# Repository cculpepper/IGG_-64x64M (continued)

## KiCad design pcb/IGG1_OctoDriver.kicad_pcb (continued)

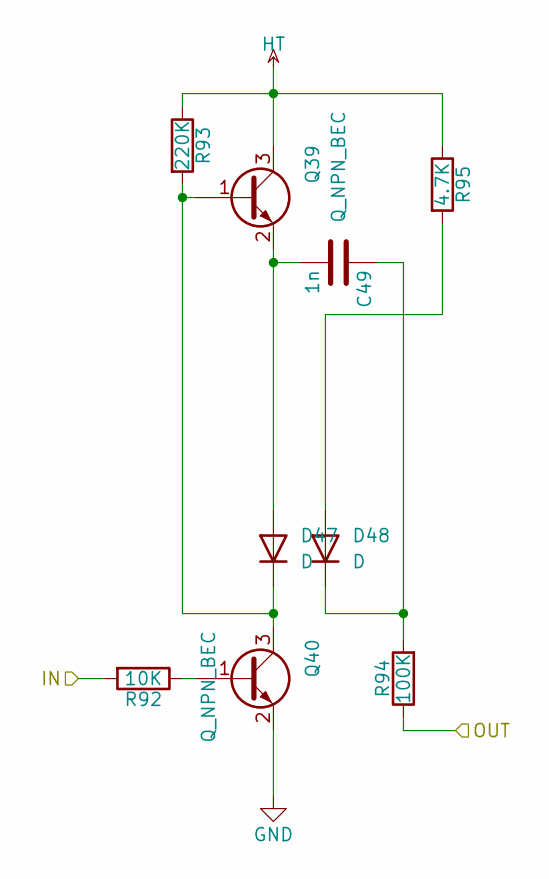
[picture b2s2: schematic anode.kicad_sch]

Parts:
C49: 1n; C_1206_3216Metric; LCSC C9196
D47, D48: D; D_SOD-323; LCSC C896450
Q39, Q40: Q_NPN_BEC; SOT-23; LCSC C20069141
R92: 10K; R_0603_1608Metric; LCSC C25804
R93: 220K; R_1206_3216Metric; LCSC C17956
R94: 100K; R_1206_3216Metric; LCSC C17900
R95: 4.7K; R_1206_3216Metric; LCSC C17936

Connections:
/AI18: R92.2; also elsewhere on the board
/AO18: R94.1; also elsewhere on the board
GND: Q40.2 (E); also elsewhere on the board
HT: Q39.3 (C), R93.1, R95.1; also elsewhere on the board
unnamed: C49.2, D47.2 (A), Q39.2 (E)
unnamed: D47.1 (K), Q39.1 (B), Q40.3 (C), R93.2
unnamed: D48.2 (A), R95.2
unnamed: C49.1, D48.1 (K), R94.2
unnamed: Q40.1 (B), R92.1

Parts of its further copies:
C30, C31, C32, C33, C34, C35, C36, C37, C38, C39, C40, C41, C42, C43, C44, C45, C46, C47, C48, C50, C51, C52, C53, C54, C55, C56, C57, C58, C59, C60, C61, C62, C63, C64, C65, C66, C67, C68, C69, C70, C71, C72, C73, C74, C75, C76, C77, C78, C79, C80, C81, C82, C83, C84, C85, C86, C87, C88, C89, C90, C91, C92, C93: 1n; C_1206_3216Metric; LCSC C9196
D9, D10, D11, D12, D13, D14, D15, D16, D17, D18, D19, D20, D21, D22, D23, D24, D25, D26, D27, D28, D29, D30, D31, D32, D33, D34, D35, D36, D37, D38, D39, D40, D41, D42, D43, D44, D45, D46, D49, D50, D51, D52, D53, D54, D55, D56, D57, D58, D59, D60, D61, D62, D63, D64, D65, D66, D67, D68, D69, D70, D71, D72, D73, D74, D75, D76, D77, D78, D79, D80, D81, D82, D83, D84, D85, D86, D87, D88, D89, D90, D91, D92, D93, D94, D95, D96, D97, D98, D99, D100, D101, D102, D103, D104, D105, D106, D107, D108, D109, D110, D111, D112, D113, D114, D115, D116, D117, D118, D119, D120, D121, D122, D123, D124, D125, D126, D127, D128, D129, D130, D131, D132, D133, D134, D135, D136: D; D_SOD-323; LCSC C896450
Q1, Q2, Q3, Q4, Q5, Q6, Q7, Q8, Q9, Q10, Q11, Q12, Q13, Q14, Q15, Q16, Q17, Q18, Q19, Q20, Q21, Q22, Q23, Q24, Q25, Q26, Q27, Q28, Q29, Q30, Q31, Q32, Q33, Q34, Q35, Q36, Q37, Q38, Q41, Q42, Q43, Q44, Q45, Q46, Q47, Q48, Q49, Q50, Q51, Q52, Q53, Q54, Q55, Q56, Q57, Q58, Q59, Q60, Q61, Q62, Q63, Q64, Q65, Q66, Q67, Q68, Q69, Q70, Q71, Q72, Q73, Q74, Q75, Q76, Q77, Q78, Q79, Q80, Q81, Q82, Q83, Q84, Q85, Q86, Q87, Q88, Q89, Q90, Q91, Q92, Q93, Q94, Q95, Q96, Q97, Q98, Q99, Q100, Q101, Q102, Q103, Q104, Q105, Q106, Q107, Q108, Q109, Q110, Q111, Q112, Q113, Q114, Q115, Q116, Q117, Q118, Q119, Q120, Q121, Q122, Q123, Q124, Q125, Q126, Q127, Q128: Q_NPN_BEC; SOT-23; LCSC C20069141
R16, R20, R24, R28, R32, R36, R40, R44, R48, R52, R56, R60, R64, R68, R72, R76, R80, R84, R88, R96, R100, R104, R108, R112, R116, R120, R124, R128, R132, R136, R140, R144, R148, R152, R156, R160, R164, R168, R172, R176, R180, R184, R188, R192, R196, R200, R204, R208, R212, R216, R220, R224, R228, R232, R236, R240, R244, R248, R252, R256, R260, R264, R268: 10K; R_0603_1608Metric; LCSC C25804
R17, R21, R25, R29, R33, R37, R41, R45, R49, R53, R57, R61, R65, R69, R73, R77, R81, R85, R89, R97, R101, R105, R109, R113, R117, R121, R125, R129, R133, R137, R141, R145, R149, R153, R157, R161, R165, R169, R173, R177, R181, R185, R189, R193, R197, R201, R205, R209, R213, R217, R221, R225, R229, R233, R237, R241, R245, R249, R253, R257, R261, R265, R269: 220K; R_1206_3216Metric; LCSC C17956
R18, R22, R26, R30, R34, R38, R42, R46, R50, R54, R58, R62, R66, R70, R74, R78, R82, R86, R90, R98, R102, R106, R110, R114, R118, R122, R126, R130, R134, R138, R142, R146, R150, R154, R158, R162, R166, R170, R174, R178, R182, R186, R190, R194, R198, R202, R206, R210, R214, R218, R222, R226, R230, R234, R238, R242, R246, R250, R254, R258, R262, R266, R270: 100K; R_1206_3216Metric; LCSC C17900
R19, R23, R27, R31, R35, R39, R43, R47, R51, R55, R59, R63, R67, R71, R75, R79, R83, R87, R91, R99, R103, R107, R111, R115, R119, R123, R127, R131, R135, R139, R143, R147, R151, R155, R159, R163, R167, R171, R175, R179, R183, R187, R191, R195, R199, R203, R207, R211, R215, R219, R223, R227, R231, R235, R239, R243, R247, R251, R255, R259, R263, R267, R271: 4.7K; R_1206_3216Metric; LCSC C17936

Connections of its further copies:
/AI1: R16.2; also elsewhere on the board
/AI2: R20.2; also elsewhere on the board
/AI3: R24.2; also elsewhere on the board
/AI4: R28.2; also elsewhere on the board
/AI5: R32.2; also elsewhere on the board
/AI6: R44.2; also elsewhere on the board
/AI7: R36.2; also elsewhere on the board
/AI8: R40.2; also elsewhere on the board
/AI9: R48.2; also elsewhere on the board
/AI10: R60.2; also elsewhere on the board
/AI11: R52.2; also elsewhere on the board
/AI12: R56.2; also elsewhere on the board
/AI13: R64.2; also elsewhere on the board
/AI14: R76.2; also elsewhere on the board
/AI15: R68.2; also elsewhere on the board
/AI16: R72.2; also elsewhere on the board
/AI17: R80.2; also elsewhere on the board
/AI19: R84.2; also elsewhere on the board
/AI20: R88.2; also elsewhere on the board
/AI21: R96.2; also elsewhere on the board
/AI22: R108.2; also elsewhere on the board
/AI23: R100.2; also elsewhere on the board
/AI24: R104.2; also elsewhere on the board
/AI25: R112.2; also elsewhere on the board
/AI26: R124.2; also elsewhere on the board
/AI27: R116.2; also elsewhere on the board
/AI28: R120.2; also elsewhere on the board
/AI29: R128.2; also elsewhere on the board
/AI30: R140.2; also elsewhere on the board
/AI31: R132.2; also elsewhere on the board
/AI32: R136.2; also elsewhere on the board
/AI33: R144.2; also elsewhere on the board
/AI34: R156.2; also elsewhere on the board
/AI35: R148.2; also elsewhere on the board
/AI36: R152.2; also elsewhere on the board
/AI37: R160.2; also elsewhere on the board
/AI38: R172.2; also elsewhere on the board
/AI39: R164.2; also elsewhere on the board
/AI40: R168.2; also elsewhere on the board
/AI41: R176.2; also elsewhere on the board
/AI42: R188.2; also elsewhere on the board
/AI43: R180.2; also elsewhere on the board
/AI44: R184.2; also elsewhere on the board
/AI45: R192.2; also elsewhere on the board
/AI46: R204.2; also elsewhere on the board
/AI47: R196.2; also elsewhere on the board
/AI48: R200.2; also elsewhere on the board
/AI49: R208.2; also elsewhere on the board
/AI50: R220.2; also elsewhere on the board
/AI51: R212.2; also elsewhere on the board
/AI52: R216.2; also elsewhere on the board
/AI53: R224.2; also elsewhere on the board
/AI54: R236.2; also elsewhere on the board
/AI55: R228.2; also elsewhere on the board
/AI56: R232.2; also elsewhere on the board
/AI57: R240.2; also elsewhere on the board
/AI58: R252.2; also elsewhere on the board
/AI59: R244.2; also elsewhere on the board
/AI60: R248.2; also elsewhere on the board
/AI61: R256.2; also elsewhere on the board
/AI62: R268.2; also elsewhere on the board
/AI63: R260.2; also elsewhere on the board
/AI64: R264.2; also elsewhere on the board
/AO1: R18.1; also elsewhere on the board
/AO2: R22.1; also elsewhere on the board
/AO3: R26.1; also elsewhere on the board
/AO4: R30.1; also elsewhere on the board
/AO5: R34.1; also elsewhere on the board
/AO6: R46.1; also elsewhere on the board
/AO7: R38.1; also elsewhere on the board
/AO8: R42.1; also elsewhere on the board
/AO9: R50.1; also elsewhere on the board
/AO10: R62.1; also elsewhere on the board
/AO11: R54.1; also elsewhere on the board
/AO12: R58.1; also elsewhere on the board
/AO13: R66.1; also elsewhere on the board
/AO14: R78.1; also elsewhere on the board
/AO15: R70.1; also elsewhere on the board
/AO16: R74.1; also elsewhere on the board
/AO17: R82.1; also elsewhere on the board
/AO19: R86.1; also elsewhere on the board
/AO20: R90.1; also elsewhere on the board
/AO21: R98.1; also elsewhere on the board
/AO22: R110.1; also elsewhere on the board
/AO23: R102.1; also elsewhere on the board
/AO24: R106.1; also elsewhere on the board
/AO25: R114.1; also elsewhere on the board
/AO26: R126.1; also elsewhere on the board
/AO27: R118.1; also elsewhere on the board
/AO28: R122.1; also elsewhere on the board
/AO29: R130.1; also elsewhere on the board
/AO30: R142.1; also elsewhere on the board
/AO31: R134.1; also elsewhere on the board
/AO32: R138.1; also elsewhere on the board
/AO33: R146.1; also elsewhere on the board
/AO34: R158.1; also elsewhere on the board
/AO35: R150.1; also elsewhere on the board
/AO36: R154.1; also elsewhere on the board
/AO37: R162.1; also elsewhere on the board
/AO38: R174.1; also elsewhere on the board
/AO39: R166.1; also elsewhere on the board
/AO40: R170.1; also elsewhere on the board
/AO41: R178.1; also elsewhere on the board
/AO42: R190.1; also elsewhere on the board
/AO43: R182.1; also elsewhere on the board
/AO44: R186.1; also elsewhere on the board
/AO45: R194.1; also elsewhere on the board
/AO46: R206.1; also elsewhere on the board
/AO47: R198.1; also elsewhere on the board
/AO48: R202.1; also elsewhere on the board
/AO49: R210.1; also elsewhere on the board
/AO50: R222.1; also elsewhere on the board
/AO51: R214.1; also elsewhere on the board
/AO52: R218.1; also elsewhere on the board
/AO53: R226.1; also elsewhere on the board
/AO54: R238.1; also elsewhere on the board
/AO55: R230.1; also elsewhere on the board
/AO56: R234.1; also elsewhere on the board
/AO57: R242.1; also elsewhere on the board
/AO58: R254.1; also elsewhere on the board
/AO59: R246.1; also elsewhere on the board
/AO60: R250.1; also elsewhere on the board
/AO61: R258.1; also elsewhere on the board
/AO62: R270.1; also elsewhere on the board
/AO63: R262.1; also elsewhere on the board
/AO64: R266.1; also elsewhere on the board
GND: Q2.2 (E), Q4.2 (E), Q6.2 (E), Q8.2 (E), Q10.2 (E), Q12.2 (E), Q14.2 (E), Q16.2 (E), Q18.2 (E), Q20.2 (E), Q22.2 (E), Q24.2 (E), Q26.2 (E), Q28.2 (E), Q30.2 (E), Q32.2 (E), Q34.2 (E), Q36.2 (E), Q38.2 (E), Q42.2 (E), Q44.2 (E), Q46.2 (E), Q48.2 (E), Q50.2 (E), Q52.2 (E), Q54.2 (E), Q56.2 (E), Q58.2 (E), Q60.2 (E), Q62.2 (E), Q64.2 (E), Q66.2 (E), Q68.2 (E), Q70.2 (E), Q72.2 (E), Q74.2 (E), Q76.2 (E), Q78.2 (E), Q80.2 (E), Q82.2 (E), Q84.2 (E), Q86.2 (E), Q88.2 (E), Q90.2 (E), Q92.2 (E), Q94.2 (E), Q96.2 (E), Q98.2 (E), Q100.2 (E), Q102.2 (E), Q104.2 (E), Q106.2 (E), Q108.2 (E), Q110.2 (E), Q112.2 (E), Q114.2 (E), Q116.2 (E), Q118.2 (E), Q120.2 (E), Q122.2 (E), Q124.2 (E), Q126.2 (E), Q128.2 (E); also elsewhere on the board
HT: Q1.3 (C), Q3.3 (C), Q5.3 (C), Q7.3 (C), Q9.3 (C), Q11.3 (C), Q13.3 (C), Q15.3 (C), Q17.3 (C), Q19.3 (C), Q21.3 (C), Q23.3 (C), Q25.3 (C), Q27.3 (C), Q29.3 (C), Q31.3 (C), Q33.3 (C), Q35.3 (C), Q37.3 (C), Q41.3 (C), Q43.3 (C), Q45.3 (C), Q47.3 (C), Q49.3 (C), Q51.3 (C), Q53.3 (C), Q55.3 (C), Q57.3 (C), Q59.3 (C), Q61.3 (C), Q63.3 (C), Q65.3 (C), Q67.3 (C), Q69.3 (C), Q71.3 (C), Q73.3 (C), Q75.3 (C), Q77.3 (C), Q79.3 (C), Q81.3 (C), Q83.3 (C), Q85.3 (C), Q87.3 (C), Q89.3 (C), Q91.3 (C), Q93.3 (C), Q95.3 (C), Q97.3 (C), Q99.3 (C), Q101.3 (C), Q103.3 (C), Q105.3 (C), Q107.3 (C), Q109.3 (C), Q111.3 (C), Q113.3 (C), Q115.3 (C), Q117.3 (C), Q119.3 (C), Q121.3 (C), Q123.3 (C), Q125.3 (C), Q127.3 (C), R17.1, R19.1, R21.1, R23.1, R25.1, R27.1, R29.1, R31.1, R33.1, R35.1, R37.1, R39.1, R41.1, R43.1, R45.1, R47.1, R49.1, R51.1, R53.1, R55.1, R57.1, R59.1, R61.1, R63.1, R65.1, R67.1, R69.1, R71.1, R73.1, R75.1, R77.1, R79.1, R81.1, R83.1, R85.1, R87.1, R89.1, R91.1, R97.1, R99.1, R101.1, R103.1, R105.1, R107.1, R109.1, R111.1, R113.1, R115.1, R117.1, R119.1, R121.1, R123.1, R125.1, R127.1, R129.1, R131.1, R133.1, R135.1, R137.1, R139.1, R141.1, R143.1, R145.1, R147.1, R149.1, R151.1, R153.1, R155.1, R157.1, R159.1, R161.1, R163.1, R165.1, R167.1, R169.1, R171.1, R173.1, R175.1, R177.1, R179.1, R181.1, R183.1, R185.1, R187.1, R189.1, R191.1, R193.1, R195.1, R197.1, R199.1, R201.1, R203.1, R205.1, R207.1, R209.1, R211.1, R213.1, R215.1, R217.1, R219.1, R221.1, R223.1, R225.1, R227.1, R229.1, R231.1, R233.1, R235.1, R237.1, R239.1, R241.1, R243.1, R245.1, R247.1, R249.1, R251.1, R253.1, R255.1, R257.1, R259.1, R261.1, R263.1, R265.1, R267.1, R269.1, R271.1; also elsewhere on the board
unnamed: C30.2, D9.2 (A), Q1.2 (E)
unnamed: D9.1 (K), Q1.1 (B), Q2.3 (C), R17.2
unnamed: D10.2 (A), R19.2
unnamed: C30.1, D10.1 (K), R18.2
unnamed: C31.2, D11.2 (A), Q3.2 (E)
unnamed: D11.1 (K), Q3.1 (B), Q4.3 (C), R21.2
unnamed: D12.2 (A), R23.2
unnamed: C31.1, D12.1 (K), R22.2
unnamed: C32.2, D13.2 (A), Q5.2 (E)
unnamed: D13.1 (K), Q5.1 (B), Q6.3 (C), R25.2
unnamed: D14.2 (A), R27.2
unnamed: C32.1, D14.1 (K), R26.2
unnamed: C33.2, D15.2 (A), Q7.2 (E)
unnamed: D15.1 (K), Q7.1 (B), Q8.3 (C), R29.2
unnamed: D16.2 (A), R31.2
unnamed: C33.1, D16.1 (K), R30.2
unnamed: C34.2, D17.2 (A), Q9.2 (E)
unnamed: D17.1 (K), Q9.1 (B), Q10.3 (C), R33.2
unnamed: D18.2 (A), R35.2
unnamed: C34.1, D18.1 (K), R34.2
unnamed: C35.2, D19.2 (A), Q11.2 (E)
unnamed: D19.1 (K), Q11.1 (B), Q12.3 (C), R37.2
unnamed: D20.2 (A), R39.2
unnamed: C35.1, D20.1 (K), R38.2
unnamed: C36.2, D21.2 (A), Q13.2 (E)
unnamed: D21.1 (K), Q13.1 (B), Q14.3 (C), R41.2
unnamed: D22.2 (A), R43.2
unnamed: C36.1, D22.1 (K), R42.2
unnamed: C37.2, D23.2 (A), Q15.2 (E)
unnamed: D23.1 (K), Q15.1 (B), Q16.3 (C), R45.2
unnamed: D24.2 (A), R47.2
unnamed: C37.1, D24.1 (K), R46.2
unnamed: C38.2, D25.2 (A), Q17.2 (E)
unnamed: D25.1 (K), Q17.1 (B), Q18.3 (C), R49.2
unnamed: D26.2 (A), R51.2
unnamed: C38.1, D26.1 (K), R50.2
unnamed: C39.2, D27.2 (A), Q19.2 (E)
unnamed: D27.1 (K), Q19.1 (B), Q20.3 (C), R53.2
unnamed: D28.2 (A), R55.2
unnamed: C39.1, D28.1 (K), R54.2
unnamed: C40.2, D29.2 (A), Q21.2 (E)
unnamed: D29.1 (K), Q21.1 (B), Q22.3 (C), R57.2
unnamed: D30.2 (A), R59.2
unnamed: C40.1, D30.1 (K), R58.2
unnamed: C41.2, D31.2 (A), Q23.2 (E)
unnamed: D31.1 (K), Q23.1 (B), Q24.3 (C), R61.2
unnamed: D32.2 (A), R63.2
unnamed: C41.1, D32.1 (K), R62.2
unnamed: C42.2, D33.2 (A), Q25.2 (E)
unnamed: D33.1 (K), Q25.1 (B), Q26.3 (C), R65.2
unnamed: D34.2 (A), R67.2
unnamed: C42.1, D34.1 (K), R66.2
unnamed: C43.2, D35.2 (A), Q27.2 (E)
unnamed: D35.1 (K), Q27.1 (B), Q28.3 (C), R69.2
unnamed: D36.2 (A), R71.2
unnamed: C43.1, D36.1 (K), R70.2
unnamed: C44.2, D37.2 (A), Q29.2 (E)
unnamed: D37.1 (K), Q29.1 (B), Q30.3 (C), R73.2
unnamed: D38.2 (A), R75.2
unnamed: C44.1, D38.1 (K), R74.2
unnamed: C45.2, D39.2 (A), Q31.2 (E)
unnamed: D39.1 (K), Q31.1 (B), Q32.3 (C), R77.2
unnamed: D40.2 (A), R79.2
unnamed: C45.1, D40.1 (K), R78.2
unnamed: C46.2, D41.2 (A), Q33.2 (E)
unnamed: D41.1 (K), Q33.1 (B), Q34.3 (C), R81.2
unnamed: D42.2 (A), R83.2
unnamed: C46.1, D42.1 (K), R82.2
unnamed: C47.2, D43.2 (A), Q35.2 (E)
unnamed: D43.1 (K), Q35.1 (B), Q36.3 (C), R85.2
unnamed: D44.2 (A), R87.2
unnamed: C47.1, D44.1 (K), R86.2
unnamed: C48.2, D45.2 (A), Q37.2 (E)
unnamed: D45.1 (K), Q37.1 (B), Q38.3 (C), R89.2
unnamed: D46.2 (A), R91.2
unnamed: C48.1, D46.1 (K), R90.2
unnamed: C50.2, D49.2 (A), Q41.2 (E)
unnamed: D49.1 (K), Q41.1 (B), Q42.3 (C), R97.2
unnamed: D50.2 (A), R99.2
unnamed: C50.1, D50.1 (K), R98.2
unnamed: C51.2, D51.2 (A), Q43.2 (E)
unnamed: D51.1 (K), Q43.1 (B), Q44.3 (C), R101.2
unnamed: D52.2 (A), R103.2
unnamed: C51.1, D52.1 (K), R102.2
unnamed: C52.2, D53.2 (A), Q45.2 (E)
unnamed: D53.1 (K), Q45.1 (B), Q46.3 (C), R105.2
unnamed: D54.2 (A), R107.2
unnamed: C52.1, D54.1 (K), R106.2
unnamed: C53.2, D55.2 (A), Q47.2 (E)
unnamed: D55.1 (K), Q47.1 (B), Q48.3 (C), R109.2
unnamed: D56.2 (A), R111.2
unnamed: C53.1, D56.1 (K), R110.2
unnamed: C54.2, D57.2 (A), Q49.2 (E)
unnamed: D57.1 (K), Q49.1 (B), Q50.3 (C), R113.2
unnamed: D58.2 (A), R115.2
unnamed: C54.1, D58.1 (K), R114.2
unnamed: C55.2, D59.2 (A), Q51.2 (E)
unnamed: D59.1 (K), Q51.1 (B), Q52.3 (C), R117.2
unnamed: D60.2 (A), R119.2
unnamed: C55.1, D60.1 (K), R118.2
unnamed: C56.2, D61.2 (A), Q53.2 (E)
unnamed: D61.1 (K), Q53.1 (B), Q54.3 (C), R121.2
unnamed: D62.2 (A), R123.2
unnamed: C56.1, D62.1 (K), R122.2
unnamed: C57.2, D63.2 (A), Q55.2 (E)
unnamed: D63.1 (K), Q55.1 (B), Q56.3 (C), R125.2
unnamed: D64.2 (A), R127.2
unnamed: C57.1, D64.1 (K), R126.2
unnamed: C58.2, D65.2 (A), Q57.2 (E)
unnamed: D65.1 (K), Q57.1 (B), Q58.3 (C), R129.2
unnamed: D66.2 (A), R131.2
unnamed: C58.1, D66.1 (K), R130.2
unnamed: C59.2, D67.2 (A), Q59.2 (E)
unnamed: D67.1 (K), Q59.1 (B), Q60.3 (C), R133.2
unnamed: D68.2 (A), R135.2
unnamed: C59.1, D68.1 (K), R134.2
unnamed: C60.2, D69.2 (A), Q61.2 (E)
unnamed: D69.1 (K), Q61.1 (B), Q62.3 (C), R137.2
unnamed: D70.2 (A), R139.2
unnamed: C60.1, D70.1 (K), R138.2
unnamed: C61.2, D71.2 (A), Q63.2 (E)
unnamed: D71.1 (K), Q63.1 (B), Q64.3 (C), R141.2
unnamed: D72.2 (A), R143.2
unnamed: C61.1, D72.1 (K), R142.2
unnamed: C62.2, D73.2 (A), Q65.2 (E)
unnamed: D73.1 (K), Q65.1 (B), Q66.3 (C), R145.2
unnamed: D74.2 (A), R147.2
unnamed: C62.1, D74.1 (K), R146.2
unnamed: C63.2, D75.2 (A), Q67.2 (E)
unnamed: D75.1 (K), Q67.1 (B), Q68.3 (C), R149.2
unnamed: D76.2 (A), R151.2
unnamed: C63.1, D76.1 (K), R150.2
unnamed: C64.2, D77.2 (A), Q69.2 (E)
unnamed: D77.1 (K), Q69.1 (B), Q70.3 (C), R153.2
unnamed: D78.2 (A), R155.2
unnamed: C64.1, D78.1 (K), R154.2
unnamed: C65.2, D79.2 (A), Q71.2 (E)
unnamed: D79.1 (K), Q71.1 (B), Q72.3 (C), R157.2
unnamed: D80.2 (A), R159.2
unnamed: C65.1, D80.1 (K), R158.2
unnamed: C66.2, D81.2 (A), Q73.2 (E)
unnamed: D81.1 (K), Q73.1 (B), Q74.3 (C), R161.2
unnamed: D82.2 (A), R163.2
unnamed: C66.1, D82.1 (K), R162.2
unnamed: C67.2, D83.2 (A), Q75.2 (E)
unnamed: D83.1 (K), Q75.1 (B), Q76.3 (C), R165.2
unnamed: D84.2 (A), R167.2
unnamed: C67.1, D84.1 (K), R166.2
unnamed: C68.2, D85.2 (A), Q77.2 (E)
unnamed: D85.1 (K), Q77.1 (B), Q78.3 (C), R169.2
unnamed: D86.2 (A), R171.2
unnamed: C68.1, D86.1 (K), R170.2
unnamed: C69.2, D87.2 (A), Q79.2 (E)
unnamed: D87.1 (K), Q79.1 (B), Q80.3 (C), R173.2
unnamed: D88.2 (A), R175.2
unnamed: C69.1, D88.1 (K), R174.2
unnamed: C70.2, D89.2 (A), Q81.2 (E)
unnamed: D89.1 (K), Q81.1 (B), Q82.3 (C), R177.2
unnamed: D90.2 (A), R179.2
unnamed: C70.1, D90.1 (K), R178.2
unnamed: C71.2, D91.2 (A), Q83.2 (E)
unnamed: D91.1 (K), Q83.1 (B), Q84.3 (C), R181.2
unnamed: D92.2 (A), R183.2
unnamed: C71.1, D92.1 (K), R182.2
unnamed: C72.2, D93.2 (A), Q85.2 (E)
unnamed: D93.1 (K), Q85.1 (B), Q86.3 (C), R185.2
unnamed: D94.2 (A), R187.2
unnamed: C72.1, D94.1 (K), R186.2
unnamed: C73.2, D95.2 (A), Q87.2 (E)
unnamed: D95.1 (K), Q87.1 (B), Q88.3 (C), R189.2
unnamed: D96.2 (A), R191.2
unnamed: C73.1, D96.1 (K), R190.2
unnamed: C74.2, D97.2 (A), Q89.2 (E)
unnamed: D97.1 (K), Q89.1 (B), Q90.3 (C), R193.2
unnamed: D98.2 (A), R195.2
unnamed: C74.1, D98.1 (K), R194.2
unnamed: C75.2, D99.2 (A), Q91.2 (E)
unnamed: D99.1 (K), Q91.1 (B), Q92.3 (C), R197.2
unnamed: D100.2 (A), R199.2
unnamed: C75.1, D100.1 (K), R198.2
unnamed: C76.2, D101.2 (A), Q93.2 (E)
unnamed: D101.1 (K), Q93.1 (B), Q94.3 (C), R201.2
unnamed: D102.2 (A), R203.2
unnamed: C76.1, D102.1 (K), R202.2
unnamed: C77.2, D103.2 (A), Q95.2 (E)
unnamed: D103.1 (K), Q95.1 (B), Q96.3 (C), R205.2
unnamed: D104.2 (A), R207.2
unnamed: C77.1, D104.1 (K), R206.2
unnamed: C78.2, D105.2 (A), Q97.2 (E)
unnamed: D105.1 (K), Q97.1 (B), Q98.3 (C), R209.2
unnamed: D106.2 (A), R211.2
unnamed: C78.1, D106.1 (K), R210.2
unnamed: C79.2, D107.2 (A), Q99.2 (E)
unnamed: D107.1 (K), Q99.1 (B), Q100.3 (C), R213.2
unnamed: D108.2 (A), R215.2
unnamed: C79.1, D108.1 (K), R214.2
unnamed: C80.2, D109.2 (A), Q101.2 (E)
unnamed: D109.1 (K), Q101.1 (B), Q102.3 (C), R217.2
unnamed: D110.2 (A), R219.2
unnamed: C80.1, D110.1 (K), R218.2
unnamed: C81.2, D111.2 (A), Q103.2 (E)
unnamed: D111.1 (K), Q103.1 (B), Q104.3 (C), R221.2
unnamed: D112.2 (A), R223.2
unnamed: C81.1, D112.1 (K), R222.2
unnamed: C82.2, D113.2 (A), Q105.2 (E)
unnamed: D113.1 (K), Q105.1 (B), Q106.3 (C), R225.2
unnamed: D114.2 (A), R227.2
unnamed: C82.1, D114.1 (K), R226.2
unnamed: C83.2, D115.2 (A), Q107.2 (E)
unnamed: D115.1 (K), Q107.1 (B), Q108.3 (C), R229.2
unnamed: D116.2 (A), R231.2
unnamed: C83.1, D116.1 (K), R230.2
unnamed: C84.2, D117.2 (A), Q109.2 (E)
unnamed: D117.1 (K), Q109.1 (B), Q110.3 (C), R233.2
unnamed: D118.2 (A), R235.2
unnamed: C84.1, D118.1 (K), R234.2
unnamed: C85.2, D119.2 (A), Q111.2 (E)
unnamed: D119.1 (K), Q111.1 (B), Q112.3 (C), R237.2
unnamed: D120.2 (A), R239.2
unnamed: C85.1, D120.1 (K), R238.2
unnamed: C86.2, D121.2 (A), Q113.2 (E)
unnamed: D121.1 (K), Q113.1 (B), Q114.3 (C), R241.2
unnamed: D122.2 (A), R243.2
unnamed: C86.1, D122.1 (K), R242.2
unnamed: C87.2, D123.2 (A), Q115.2 (E)
unnamed: D123.1 (K), Q115.1 (B), Q116.3 (C), R245.2
unnamed: D124.2 (A), R247.2
unnamed: C87.1, D124.1 (K), R246.2
unnamed: C88.2, D125.2 (A), Q117.2 (E)
unnamed: D125.1 (K), Q117.1 (B), Q118.3 (C), R249.2
unnamed: D126.2 (A), R251.2
unnamed: C88.1, D126.1 (K), R250.2
unnamed: C89.2, D127.2 (A), Q119.2 (E)
unnamed: D127.1 (K), Q119.1 (B), Q120.3 (C), R253.2
unnamed: D128.2 (A), R255.2
unnamed: C89.1, D128.1 (K), R254.2
unnamed: C90.2, D129.2 (A), Q121.2 (E)
unnamed: D129.1 (K), Q121.1 (B), Q122.3 (C), R257.2
unnamed: D130.2 (A), R259.2
unnamed: C90.1, D130.1 (K), R258.2
unnamed: C91.2, D131.2 (A), Q123.2 (E)
unnamed: D131.1 (K), Q123.1 (B), Q124.3 (C), R261.2
unnamed: D132.2 (A), R263.2
unnamed: C91.1, D132.1 (K), R262.2
unnamed: C92.2, D133.2 (A), Q125.2 (E)
unnamed: D133.1 (K), Q125.1 (B), Q126.3 (C), R265.2
unnamed: D134.2 (A), R267.2
unnamed: C92.1, D134.1 (K), R266.2
unnamed: C93.2, D135.2 (A), Q127.2 (E)
unnamed: D135.1 (K), Q127.1 (B), Q128.3 (C), R269.2
unnamed: D136.2 (A), R271.2
unnamed: C93.1, D136.1 (K), R270.2
unnamed: Q2.1 (B), R16.1
unnamed: Q4.1 (B), R20.1
unnamed: Q6.1 (B), R24.1
unnamed: Q8.1 (B), R28.1
unnamed: Q10.1 (B), R32.1
unnamed: Q12.1 (B), R36.1
unnamed: Q14.1 (B), R40.1
unnamed: Q16.1 (B), R44.1
unnamed: Q18.1 (B), R48.1
unnamed: Q20.1 (B), R52.1
unnamed: Q22.1 (B), R56.1
unnamed: Q24.1 (B), R60.1
unnamed: Q26.1 (B), R64.1
unnamed: Q28.1 (B), R68.1
unnamed: Q30.1 (B), R72.1
unnamed: Q32.1 (B), R76.1
unnamed: Q34.1 (B), R80.1
unnamed: Q36.1 (B), R84.1
unnamed: Q38.1 (B), R88.1
unnamed: Q42.1 (B), R96.1
unnamed: Q44.1 (B), R100.1
unnamed: Q46.1 (B), R104.1
unnamed: Q48.1 (B), R108.1
unnamed: Q50.1 (B), R112.1
unnamed: Q52.1 (B), R116.1
unnamed: Q54.1 (B), R120.1
unnamed: Q56.1 (B), R124.1
unnamed: Q58.1 (B), R128.1
unnamed: Q60.1 (B), R132.1
unnamed: Q62.1 (B), R136.1
unnamed: Q64.1 (B), R140.1
unnamed: Q66.1 (B), R144.1
unnamed: Q68.1 (B), R148.1
unnamed: Q70.1 (B), R152.1
unnamed: Q72.1 (B), R156.1
unnamed: Q74.1 (B), R160.1
unnamed: Q76.1 (B), R164.1
unnamed: Q78.1 (B), R168.1
unnamed: Q80.1 (B), R172.1
unnamed: Q82.1 (B), R176.1
unnamed: Q84.1 (B), R180.1
unnamed: Q86.1 (B), R184.1
unnamed: Q88.1 (B), R188.1
unnamed: Q90.1 (B), R192.1
unnamed: Q92.1 (B), R196.1
unnamed: Q94.1 (B), R200.1
unnamed: Q96.1 (B), R204.1
unnamed: Q98.1 (B), R208.1
unnamed: Q100.1 (B), R212.1
unnamed: Q102.1 (B), R216.1
unnamed: Q104.1 (B), R220.1
unnamed: Q106.1 (B), R224.1
unnamed: Q108.1 (B), R228.1
unnamed: Q110.1 (B), R232.1
unnamed: Q112.1 (B), R236.1
unnamed: Q114.1 (B), R240.1
unnamed: Q116.1 (B), R244.1
unnamed: Q118.1 (B), R248.1
unnamed: Q120.1 (B), R252.1
unnamed: Q122.1 (B), R256.1
unnamed: Q124.1 (B), R260.1
unnamed: Q126.1 (B), R264.1
unnamed: Q128.1 (B), R268.1

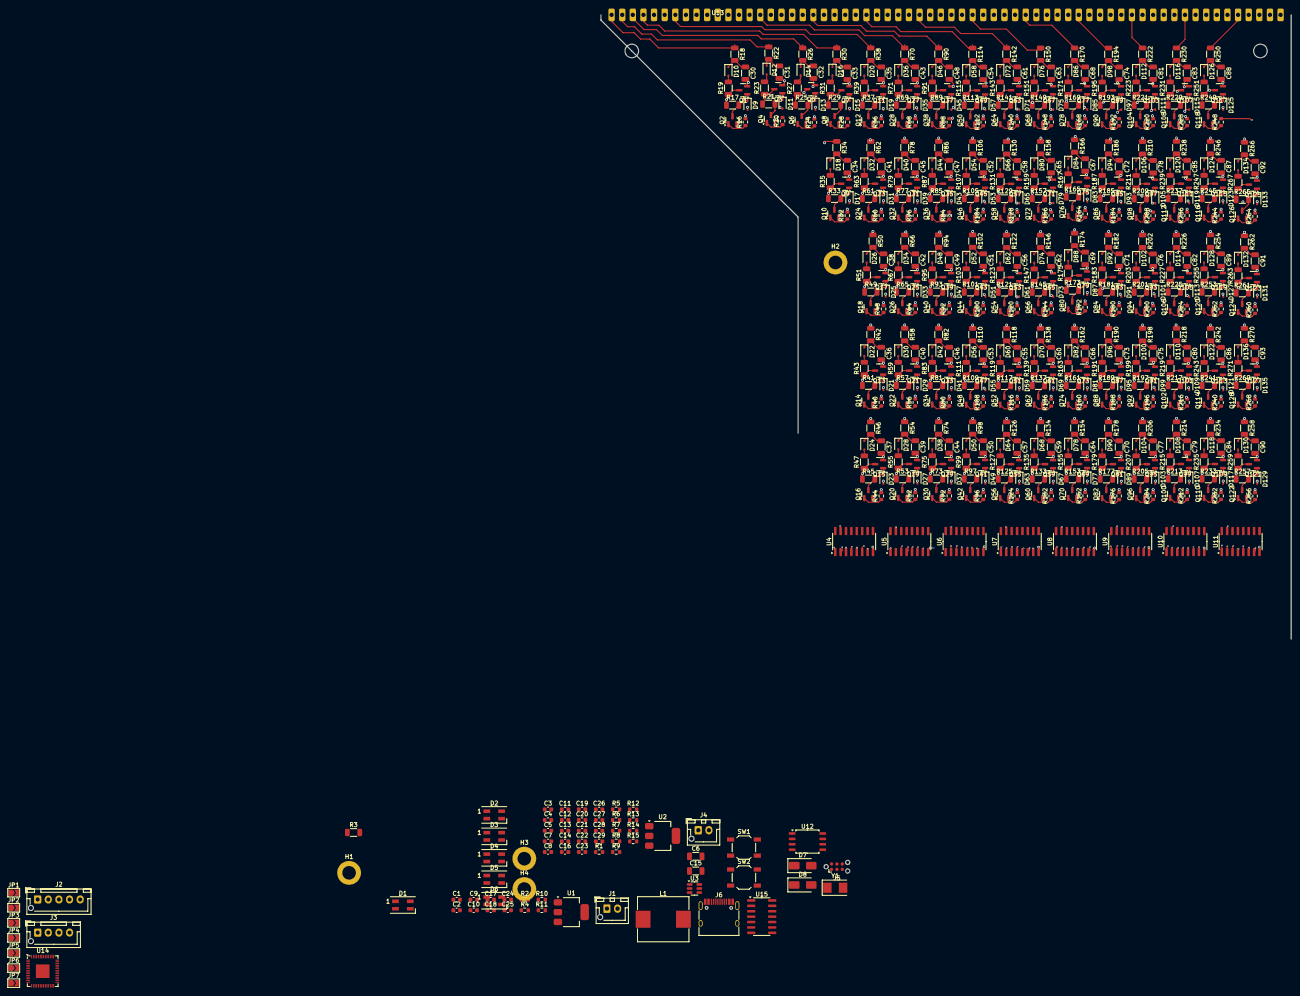
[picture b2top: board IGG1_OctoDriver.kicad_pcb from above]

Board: 4 copper layers, 162.5 x 147.0 mm, 664 parts (0 on the bottom side), 514 nets.

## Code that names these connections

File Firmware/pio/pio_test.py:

import array, time
from machine import Pin
import rp2


NUM_LEDS = 8

D1_PIN = 0
NUM_DAT_PINS = 8
SHCP_PIN = 10
EN_5V_PIN = 11
TX_LED_PIN = 12

K_RST_PIN = 14
K_CLK_PIN = 15
SR_MC_PIN = 16
SR_STCP_PIN = 17
SR_OE_PIN = 18
HV_EN_PIN = 25

HV_V_ADC_PIN = 0
BAT_V_PIN = 1
HV_EN = Pin(HV_EN_PIN, Pin.OUT)
print("Turning on HV")
HV_EN.value(1)
time.sleep_ms(100)

print("Turning off HV")
HV_EN.value(0)
time.sleep_ms(100)
print("Turning on HV")
HV_EN.value(1)
time.sleep_ms(100)
K_RST_BIT = 0x1 # Inverted!
K_CLK_BIT = 0x2 # Inverted!
SR_MC_BIT = 0x4
SR_STCP_BIT = 0x8
SR_OE_BIT = 0x10

#K_RST goes to an or gate to the reset singnal
#The 4017s need a high on the reset, and increment with a going high pulse on the clock
RESET_KATHODE_BIT_A = K_CLK_BIT
RESET_KATHODE_BIT_B = K_RST_BIT + K_CLK_BIT 

RESET_ANODE_BIT_A = 0
RESET_ANODE_BIT_B = SR_MC_BIT + SR_STCP_BIT
RESET_STATE_A = RESET_KATHODE_BIT_A + RESET_ANODE_BIT_A
RESET_STATE_B = RESET_KATHODE_BIT_B + RESET_ANODE_BIT_B

#The anodes are 74AHCT595
# MR being to zero should reset all the anode drivers
# SR_STCP clocks over the SR outputs into the outputs on a positive pulse
# SHCP clocks the input data over on a positive pulse
# SR_OE enables the outputs, otherwise are in high-Z

CLOCKING_IN_DATA_STATE = SR_MC_BIT + K_RST_BIT + K_CLK_BIT

DATA_DONE_CLOCKING_SEND_OUT_A = SR_MC_BIT + SR_OE_BIT + K_RST_BIT

#Keep from reset, clock the shift_register to the output
DATA_DONE_CLOCKING_SEND_OUT_B = SR_MC_BIT + SR_STCP_BIT + SR_OE_BIT + K_RST_BIT

DATA_DONE_CLOCKING_SEND_OUT_C = SR_MC_BIT + SR_STCP_BIT  + K_RST_BIT





@rp2.asm_pio(sideset_init=rp2.PIO.OUT_LOW, out_init=[rp2.PIO.OUT_LOW,] * NUM_DAT_PINS, set_init = [rp2.PIO.OUT_LOW, ] * 5, out_shiftdir=rp2.PIO.SHIFT_LEFT, autopull=True, pull_thresh=32)
def iggx_pio():
    K_RST_BIT = 0x1
    K_CLK_BIT = 0x2
    SR_MC_BIT = 0x4
    SR_STCP_BIT = 0x8
    SR_OE_BIT = 0x10


    DONT_RESET_KATHODE = K_RST_BIT # Inverter on this pin
    DONT_CLOCK_KATHODE = K_CLK_BIT # Keep the clock high (really a low to the chip)
    CLOCK_KATHODE = 0 # Send the clock low (really a high to the chip
    
    DONT_RESET_ANODE_SR = SR_MC_BIT
    RESET_ANODE_SR = 0
    
    #K_RST goes to an or gate to the reset singnal
    #The 4017s need a high on the reset, and increment with a going high pulse on the clock
    RESET_KATHODE_BIT_A = DONT_RESET_KATHODE  + DONT_CLOCK_KATHODE
    RESET_KATHODE_BIT_B = DONT_CLOCK_KATHODE
    

    RESET_ANODE_BIT_A = RESET_ANODE_SR
    RESET_ANODE_BIT_B = DONT_RESET_ANODE_SR + SR_STCP_BIT
    
    RESET_STATE_A = RESET_KATHODE_BIT_A + RESET_ANODE_BIT_A + SR_OE_BIT
    RESET_STATE_B = RESET_KATHODE_BIT_B + RESET_ANODE_BIT_B + SR_OE_BIT

    #The anodes are 74AHCT595
    # MR being to zero should reset all the anode drivers
    # SR_STCP clocks over the SR outputs into the outputs on a positive pulse
    # SHCP clocks the input data over on a positive pulse
    # SR_OE enables the outputs, otherwise are in high-Z

    CLOCKING_IN_DATA_STATE = DONT_RESET_ANODE_SR + DONT_RESET_KATHODE + DONT_CLOCK_KATHODE

    # Don't reset the K, turn off output, clock the shift to output, and clock the Kathode
    DATA_DONE_CLOCKING_SEND_OUT_A = DONT_RESET_KATHODE + SR_OE_BIT + DONT_RESET_ANODE_SR

    #Don't reset K, Keep the shift clocking to output, but enable output
    DATA_DONE_CLOCKING_SEND_OUT_B = DONT_RESET_KATHODE + CLOCK_KATHODE + SR_OE_BIT + DONT_RESET_ANODE_SR + SR_STCP_BIT

    DATA_DONE_CLOCKING_SEND_OUT_C = DONT_RESET_KATHODE + DONT_RESET_ANODE_SR + DONT_CLOCK_KATHODE
    
    DATA_DONE_CLOCKING_SEND_OUT_D = DONT_RESET_KATHODE + DONT_RESET_ANODE_SR + DONT_CLOCK_KATHODE
    
    # 0x01 is KRST, 02 is KCLK, 04 is MC, 08 is STCP
    #0x01:  Just KCLK 2: Just KRST, 4: Both KCLK and KRST, 8: Same as 4, 10: K_CLK, KRST, OE, Side: KCLK, KRST, SHCP
    
    set(pins, RESET_STATE_A) .side(0) [7]
    set(pins, RESET_STATE_B) .side(1) [7]
    wrap_target()
    set(x, 8) .side(0)  # TODO Check this
    set(pins, CLOCKING_IN_DATA_STATE) .side(0)
    label("clock_out")
    out(pins, 8) .side(0)
    nop() .side(1) # side set here
    nop() .side(0)
    jmp(x_dec,"clock_out") .side(0)

    label("output")
    set(pins, DATA_DONE_CLOCKING_SEND_OUT_A) .side(0) [7]
    set(pins, DATA_DONE_CLOCKING_SEND_OUT_B) .side(0) [7]
    set(pins, DATA_DONE_CLOCKING_SEND_OUT_C) .side(0) [7]
    set(pins, DATA_DONE_CLOCKING_SEND_OUT_D) .side(0) [7]
    nop() .side(0) [7]

    wrap()


# Create the StateMachine with the ws2812 program, outputting on Pin(22).
#sm = rp2.StateMachine(0, iggx_pio, freq=8_000_000, sideset_base=Pin(SHCP_PIN), out_base=Pin(D1_PIN), set_base=Pin(K_RST_PIN), pull_thresh=32)
sm = rp2.StateMachine(0, iggx_pio, freq=1_000_000, sideset_base=Pin(SHCP_PIN), out_base=Pin(D1_PIN), set_base=Pin(K_RST_PIN), pull_thresh=32)

# Start the StateMachine, it will wait for data on its FIFO.
sm.active(1)

# Display a pattern on the LEDs via an array of LED RGB values.
ar = array.array("I", [0 for _ in range(NUM_LEDS)])

a = [0] * 8
a = 0
while True:
    for i in range(64):
        sm.put(i, 8)
    #time.sleep_ms(1)

# Fade out.
for i in range(24):
    for j in range(NUM_LEDS):
        ar[j] >>= 1
    sm.put(ar, 8)
    time.sleep_ms(50)

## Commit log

2024-03-15 Updated stuff to latest version, started work
2024-05-07 Added kathode driver
2024-05-09 Finished the transistor grid
2024-05-14 Added datasheets, started adding the pcb outline
2024-05-19 Added footprint for board
2024-05-21 Started work on layout
2024-05-27 Lots of routing done
2024-05-28 Finished the kathode driver, onto the anodes
2024-05-29 Schematic almost done for anode
2024-05-30 Schematic of anode basically done, started layout
2024-05-31 Pretty far on the anode layout
2024-05-31 Added design files for the kathode, mods to the anode board
2024-05-31 Cleaned out some stuff that insn't necessarily relevant to me
2024-05-31 Added a github page, maybe
2024-05-31 Rename page
2024-05-31 Added indebx
2024-05-31 Added back the PCB
2024-05-31 Added sch to kicanvas
2024-05-31 htns
2024-05-31 ADded js
2024-05-31 Added pcb to index
2024-05-31 combined the pcbs, now to relayout. :(
2024-06-02 almost done
2024-06-03 progress!
2024-06-03 Added switch
2024-06-03 Commit to xfer to other computer
2024-06-03 modified one pin
2024-06-04 Push to other computer to edit footprint
2024-06-04 added the footprint for the SMDnuts
2024-06-09 Added mechanicDDDDl stuff, case, etc
2024-06-21 Commit before pulling firmware and redoing
2024-07-05 Firmware is getting there, new power supply helps
2024-11-03 Added python code, it works
